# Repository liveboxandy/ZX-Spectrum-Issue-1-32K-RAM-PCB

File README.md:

This is a Kicad 10 project and was only used to create an ibom to assist in the debugging of faulty boards. Use at your own risk.

Kicad does not like handrawn tracks, it only like straight lines so I have followed the route for each track but it does not track exactly but close enough for the user to find the track when debugging.

If a track originally went between two pins on the front side, it still does.
If it went between two traces it still goes between the same two traces.

The ZX Spectrum Issue 1 32K RAM PCB used has an MFG date of 1982 and has a silkscreen FAB revision of SRC091, a topside FAB revision of SRC080 A and a solder side FAB revision of SRC097 B.

The created schematic was based on the physical layout of a raw PCB with known components. The resistor values were taken from a image of a populated PCB but it was impossible to determine the values of the capacitors used so I used the values from a ZX Spectrum Issue 2 schematic 32K Expansion for the smoothing caps (C3-C10). The values of C1 and C2 are also the values used in the Issue 2 schematic.

Note that the address lines A0 to A14 through the LS157 to the RAM chips do not appear to route as expected but agree with the PCB tracking. 

I would not use these gerbers to manufacture a PCB without a lot more checking.

Have fun.

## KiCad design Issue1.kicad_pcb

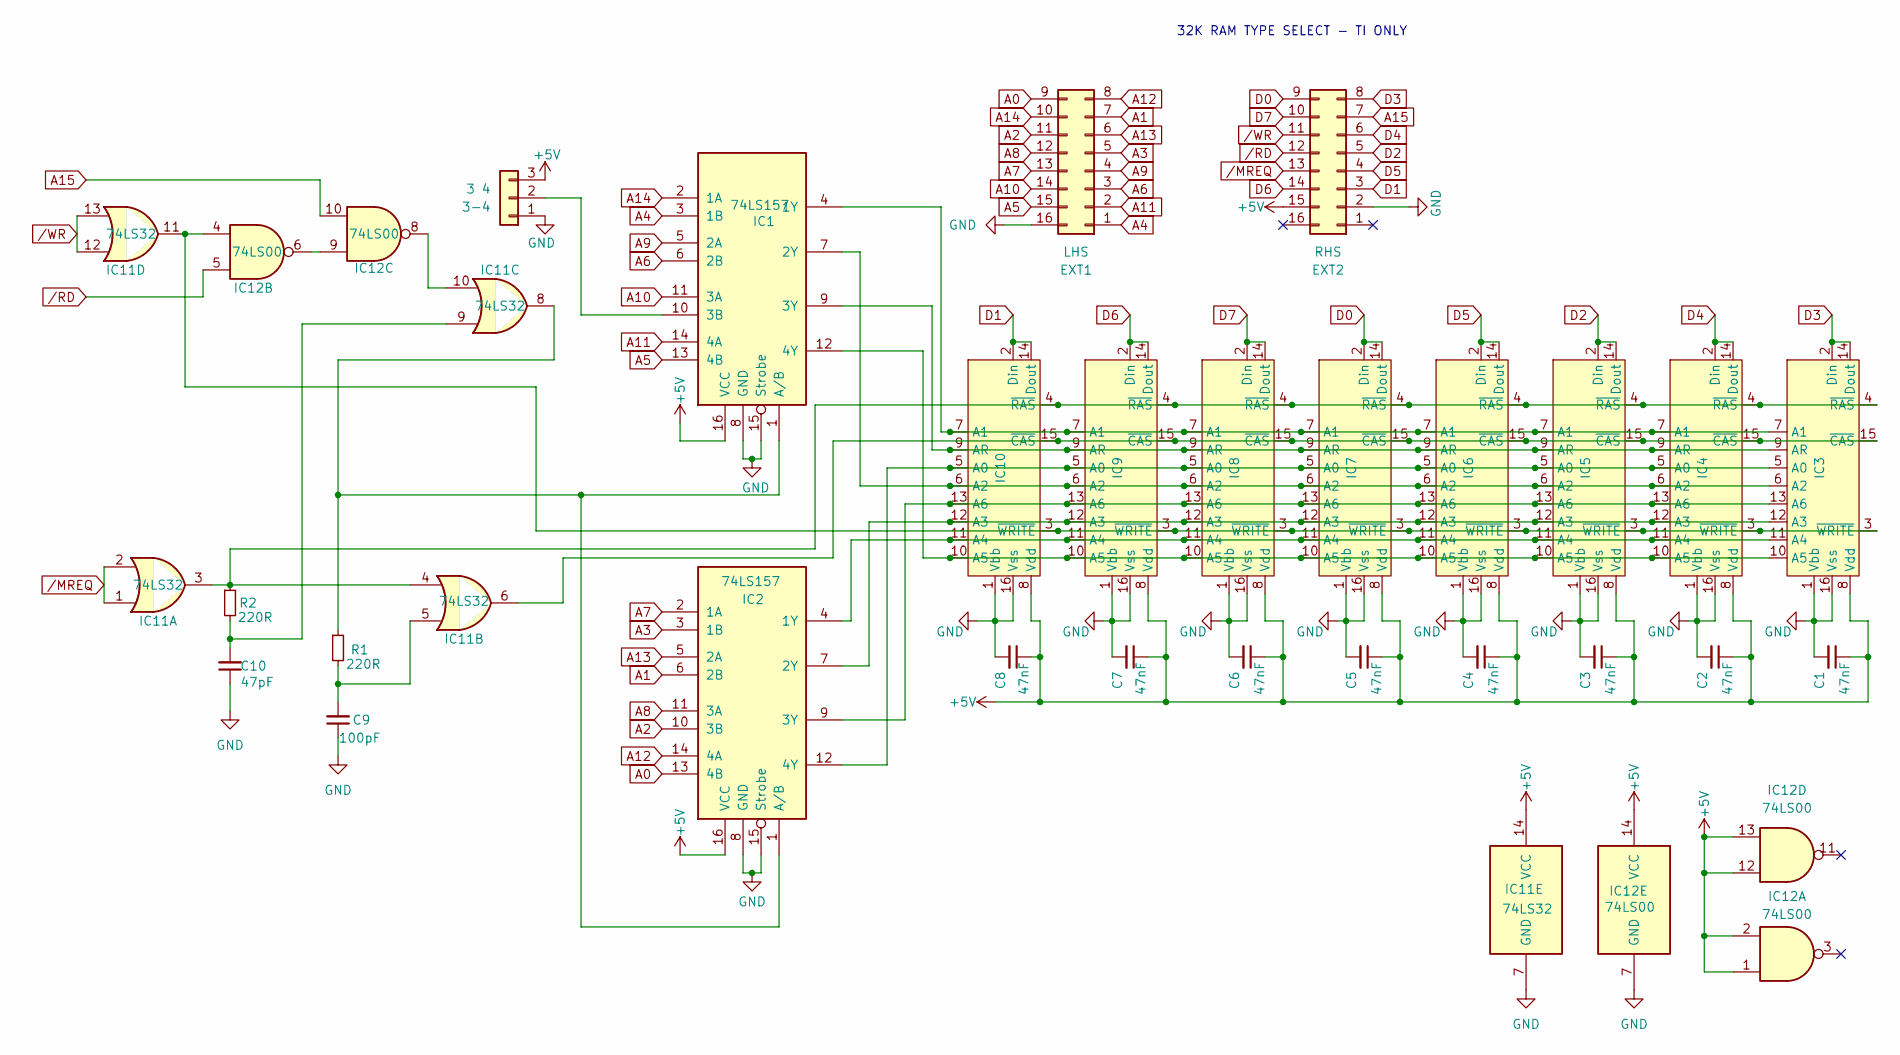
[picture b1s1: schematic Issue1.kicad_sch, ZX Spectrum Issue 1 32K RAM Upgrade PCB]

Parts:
3-4: 3 4; PinSocket_1x03_P2.54mm_Vertical
C1, C2, C3, C4, C5, C6, C7, C8: 47nF; C_Disc_D4.7mm_W2.5mm_P5.00mm
C9: 100pF; C_Axial_L7.8mm_D2.4mm_P12.70mm_Horizontal
C10: 47pF; C_Axial_L7.8mm_D2.4mm_P12.70mm_Horizontal
EXT1: LHS; DIP-16_W7.62mm_Socket
EXT2: RHS; DIP-16_W7.62mm_Socket
IC1, IC2: 74LS157; DIP-16_W7.62mm
IC3, IC4, IC5, IC6, IC7, IC8, IC9, IC10: 4532; DIP-16_W7.62mm
IC11: 74LS32; DIP-14_W7.62mm
IC12: 74LS00; DIP-14_W7.62mm
R1, R2: 220R; R_Axial_L7.8mm_D2.4mm_P12.7mm_Horizontal

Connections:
+5V: 3-4.3, C1.1, C2.1, C3.1, C4.1, C5.1, C6.1, C7.1, C8.1, EXT2.15, IC1.16 (VCC), IC2.16 (VCC), IC3.8 (Vdd), IC4.8 (Vdd), IC5.8 (Vdd), IC6.8 (Vdd), IC7.8 (Vdd), IC8.8 (Vdd), IC9.8 (Vdd), IC10.8 (Vdd), IC11.14 (VCC), IC12.1, IC12.2, IC12.12, IC12.13, IC12.14 (VCC)
A0: EXT1.9, IC2.13 (4B)
A1: EXT1.7, IC2.6 (2B)
A2: EXT1.11, IC2.10 (3B)
A3: EXT1.5, IC2.3 (1B)
A4: EXT1.1, IC1.3 (1B)
A5: EXT1.15, IC1.13 (4B)
A6: EXT1.3, IC1.6 (2B)
A7: EXT1.13, IC2.2 (1A)
A8: EXT1.12, IC2.11 (3A)
A9: EXT1.4, IC1.5 (2A)
A10: EXT1.14, IC1.11 (3A)
A11: EXT1.2, IC1.14 (4A)
A12: EXT1.8, IC2.14 (4A)
A13: EXT1.6, IC2.5 (2A)
A14: EXT1.10, IC1.2 (1A)
A15: EXT2.7, IC12.10
D0: EXT2.9, IC7.2 (Din), IC7.14 (Dout)
D1: EXT2.3, IC10.2 (Din), IC10.14 (Dout)
D2: EXT2.5, IC5.2 (Din), IC5.14 (Dout)
D3: EXT2.8, IC3.2 (Din), IC3.14 (Dout)
D4: EXT2.6, IC4.2 (Din), IC4.14 (Dout)
D5: EXT2.4, IC6.2 (Din), IC6.14 (Dout)
D6: EXT2.14, IC9.2 (Din), IC9.14 (Dout)
D7: EXT2.10, IC8.2 (Din), IC8.14 (Dout)
GND: 3-4.1, C1.2, C2.2, C3.2, C4.2, C5.2, C6.2, C7.2, C8.2, C9.1, C10.1, EXT1.16, EXT2.2, IC1.8 (GND), IC1.15 (Strobe), IC2.8 (GND), IC2.15 (Strobe), IC3.1 (Vbb), IC3.16 (Vss), IC4.1 (Vbb), IC4.16 (Vss), IC5.1 (Vbb), IC5.16 (Vss), IC6.1 (Vbb), IC6.16 (Vss), IC7.1 (Vbb), IC7.16 (Vss), IC8.1 (Vbb), IC8.16 (Vss), IC9.1 (Vbb), IC9.16 (Vss), IC10.1 (Vbb), IC10.16 (Vss), IC11.7 (GND), IC12.7 (GND)
unnamed: 3-4.2, IC1.10 (3B)
unnamed: C9.2, IC11.5, R1.2
unnamed: C10.2, IC11.9, R2.2
unnamed: IC1.4 (1Y), IC3.7 (A1), IC4.7 (A1), IC5.7 (A1), IC6.7 (A1), IC7.7 (A1), IC8.7 (A1), IC9.7 (A1), IC10.7 (A1)
unnamed: IC1.7 (2Y), IC3.6 (A2), IC4.6 (A2), IC5.6 (A2), IC6.6 (A2), IC7.6 (A2), IC8.6 (A2), IC9.6 (A2), IC10.6 (A2)
unnamed: IC1.9 (3Y), IC3.9 (AR), IC4.9 (AR), IC5.9 (AR), IC6.9 (AR), IC7.9 (AR), IC8.9 (AR), IC9.9 (AR), IC10.9 (AR)
unnamed: IC1.12 (4Y), IC3.10 (A5), IC4.10 (A5), IC5.10 (A5), IC6.10 (A5), IC7.10 (A5), IC8.10 (A5), IC9.10 (A5), IC10.10 (A5)
unnamed: IC1.1 (A/B), IC2.1 (A/B), IC11.8, R1.1
unnamed: IC2.12 (4Y), IC3.5 (A0), IC4.5 (A0), IC5.5 (A0), IC6.5 (A0), IC7.5 (A0), IC8.5 (A0), IC9.5 (A0), IC10.5 (A0)
unnamed: IC2.7 (2Y), IC3.12 (A3), IC4.12 (A3), IC5.12 (A3), IC6.12 (A3), IC7.12 (A3), IC8.12 (A3), IC9.12 (A3), IC10.12 (A3)
unnamed: IC2.4 (1Y), IC3.11 (A4), IC4.11 (A4), IC5.11 (A4), IC6.11 (A4), IC7.11 (A4), IC8.11 (A4), IC9.11 (A4), IC10.11 (A4)
unnamed: IC2.9 (3Y), IC3.13 (A6), IC4.13 (A6), IC5.13 (A6), IC6.13 (A6), IC7.13 (A6), IC8.13 (A6), IC9.13 (A6), IC10.13 (A6)
unnamed: IC3.15 (~CAS), IC4.15 (~CAS), IC5.15 (~CAS), IC6.15 (~CAS), IC7.15 (~CAS), IC8.15 (~CAS), IC9.15 (~CAS), IC10.15 (~CAS), IC11.6
unnamed: IC3.4 (~RAS), IC4.4 (~RAS), IC5.4 (~RAS), IC6.4 (~RAS), IC7.4 (~RAS), IC8.4 (~RAS), IC9.4 (~RAS), IC10.4 (~RAS), IC11.3, IC11.4, R2.1
unnamed: IC3.3 (~WRITE), IC4.3 (~WRITE), IC5.3 (~WRITE), IC6.3 (~WRITE), IC7.3 (~WRITE), IC8.3 (~WRITE), IC9.3 (~WRITE), IC10.3 (~WRITE), IC11.11, IC12.4
unnamed: IC11.10, IC12.8
unnamed: IC12.6, IC12.9
/MREQ: EXT2.13, IC11.1, IC11.2
/RD: EXT2.12, IC12.5

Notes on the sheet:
32K RAM TYPE SELECT - TI ONLY

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
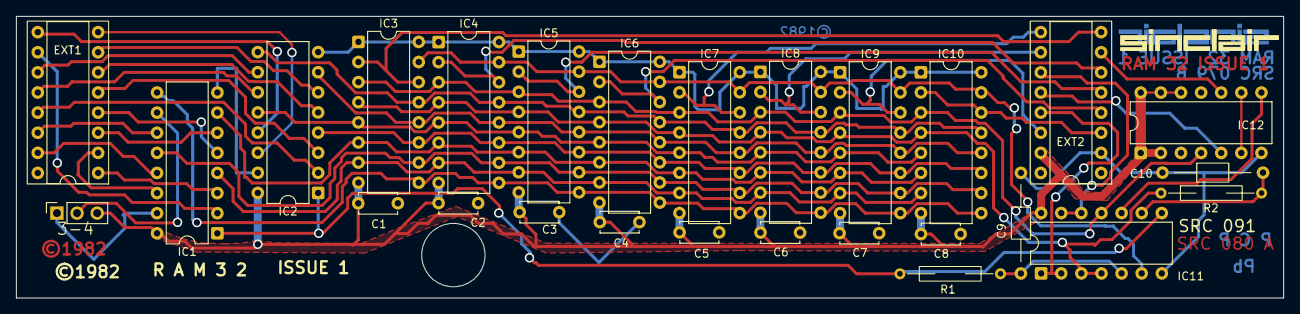
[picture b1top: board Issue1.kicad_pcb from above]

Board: 2 copper layers, 160.0 x 35.6 mm, 27 parts (0 on the bottom side), 46 nets.

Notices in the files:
Issue1.kicad_pcb:
©1982
